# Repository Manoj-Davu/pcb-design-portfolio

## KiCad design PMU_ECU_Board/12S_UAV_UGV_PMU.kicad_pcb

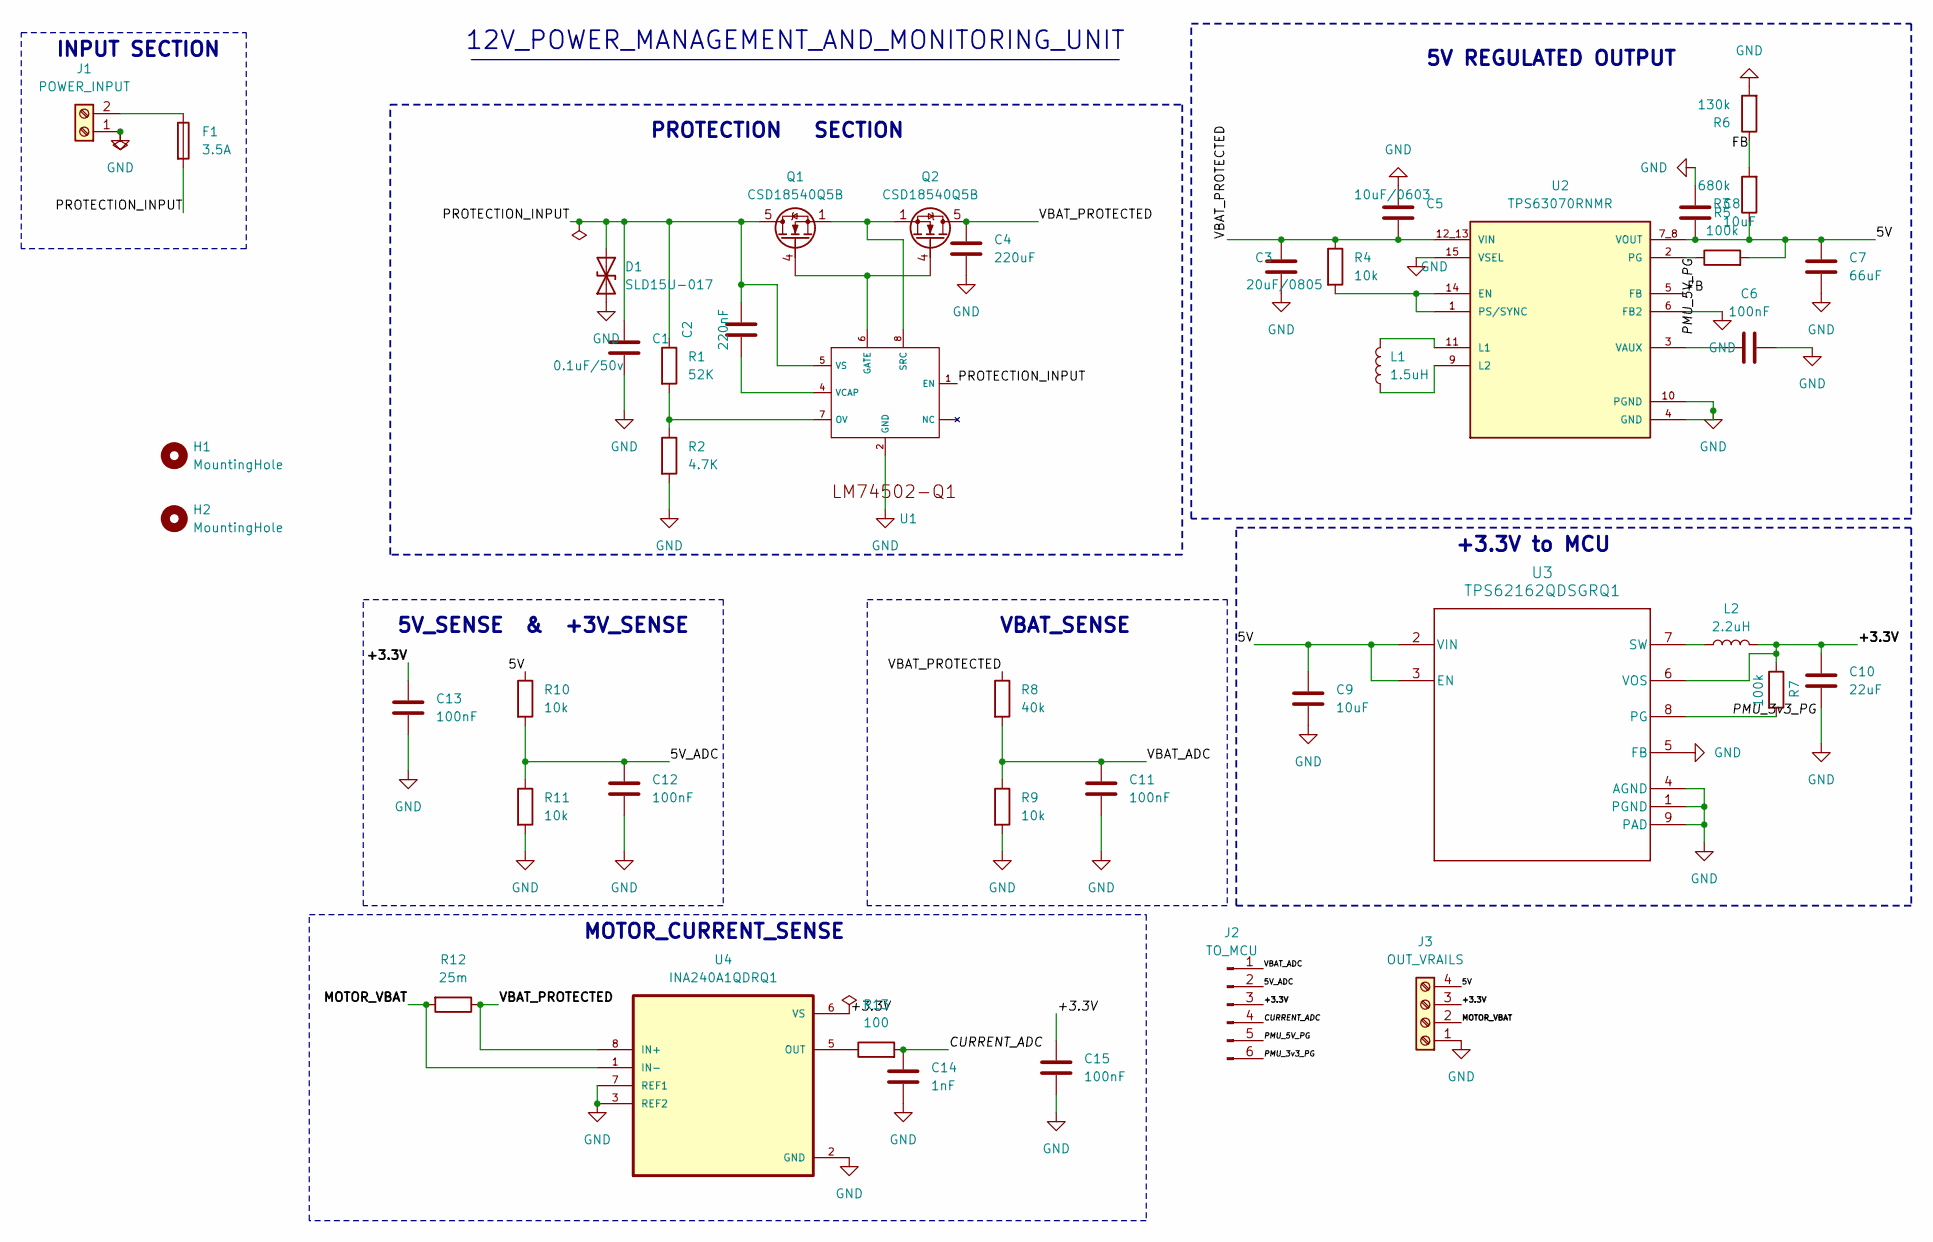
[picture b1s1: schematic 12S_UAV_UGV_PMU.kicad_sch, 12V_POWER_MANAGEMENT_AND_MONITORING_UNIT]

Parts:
C1: 0.1uF/50v; C_0603_1608Metric
C2: 220nF; C_0603_1608Metric
C3: 20uF/0805; C_0805_2012Metric
C4: 220uF; C_0603_1608Metric
C5: 10uF/0603; C_0603_1608Metric
C6, C11, C12, C13, C15: 100nF; C_0603_1608Metric
C7: 66uF; C_0805_2012Metric
C8, C9: 10uF; C_0805_2012Metric
C10: 22uF; C_0805_2012Metric
C14: 1nF; C_0603_1608Metric
D1: SLD15U-017; D_P600_R-6_P12.70mm_Horizontal
F1: 3.5A; Fuseholder_Clip-5x20mm_Littelfuse_100_Inline_P20.50x4.60mm_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
H1, H2: MountingHole; MountingHole_2.2mm_M2
J1: POWER_INPUT; TerminalBlock_Phoenix_MKDS-1,5-2-5.08_1x02_P5.08mm_Horizont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
J2: TO_MCU; PinHeader_1x06_P2.54mm_Vertical
J3: OUT_VRAILS; TerminalBlock_Phoenix_MKDS-1,5-4-5.08_1x04_P5.08mm_Horizont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
L1: 1.5uH; L_0603_1608Metric
L2: 2.2uH; L_0603_1608Metric
Q1, Q2: CSD18540Q5B; TDSON-8-1
R1: 52K; R_0603_1608Metric
R2: 4.7K; R_0603_1608Metric
R3: 680k; R_0603_1608Metric
R4, R9, R10, R11: 10k; R_0603_1608Metric
R5, R7: 100k; R_0603_1608Metric
R6: 130k; R_0603_1608Metric
R8: 40k; R_0603_1608Metric
R12: 25m; R_2512_6332Metric
R13: 100; R_0603_1608Metric
U1: SOT65P280X110-8N
U2: TPS63070RNMR; VREG_TPS63070RNMR; PARTREV B
U3: TPS62162QDSGRQ1
U4: INA240A1QDRQ1; SOIC127P599X175-8N

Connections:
/5V: C7.1, C8.2, C9.1, J3.4, R3.1, R5.2, R10.1, U2.7_8 (VOUT), U3.2 (VIN), U3.3 (EN)
/5V_ADC: C12.1, J2.2, R10.2, R11.1
/+3.3V: C10.1, C13.1, C15.1, J2.3, J3.3, L2.2, R7.1, U3.6 (VOS), U4.6 (VS)
/CURRENT_ADC: C14.1, J2.4, R13.2
/FB: R3.2, R6.1, U2.5 (FB)
/MOTOR_VBAT: J3.2, R12.2, U4.1 (IN-)
/PMU_3v3_PG: J2.6, R7.2, U3.8 (PG)
/PMU_5V_PG: J2.5, R5.1, U2.2 (PG)
/PROTECTION_INPUT: C1.1, C2.2, D1.2 (A2), F1.2, Q1.5 (D), R1.1, U1.1 (EN), U1.5 (VS)
/VBAT_ADC: C11.1, J2.1, R8.2, R9.1
/VBAT_PROTECTED: C3.1, C4.2, C5.1, Q2.5 (D), R4.1, R8.1, R12.1, U2.12_13 (VIN), U4.8 (IN+)
GND: C1.2, C3.2, C4.1, C5.2, C6.2, C7.2, C8.1, C9.2, C10.2, C11.2, C12.2, C13.2, C14.2, C15.2, D1.1 (A1), J1.1, J3.1, R2.2, R6.2, R9.2, R11.2, U1.2 (GND), U2.4 (GND), U2.6 (FB2), U2.10 (PGND), U2.15 (VSEL), U3.1 (PGND), U3.4 (AGND), U3.5 (FB), U3.9 (PAD), U4.2 (GND), U4.3 (REF2), U4.7 (REF1)
unnamed: F1.1, J1.2
unnamed: Q1.4 (G), Q2.4 (G), U1.6 (GATE)
unnamed: R1.2, R2.1, U1.7 (OV)
unnamed: Q1.1 (S), Q1.2 (S), Q1.3 (S), Q2.1 (S), Q2.2 (S), Q2.3 (S), U1.8 (SRC)
unnamed: C2.1, U1.4 (VCAP)
unnamed: R4.2, U2.1 (PS/SYNC), U2.14 (EN)
unnamed: L1.2, U2.11 (L1)
unnamed: L1.1, U2.9 (L2)
unnamed: C6.1, U2.3 (VAUX)
unnamed: L2.1, U3.7 (SW)
unnamed: R13.1, U4.5 (OUT)

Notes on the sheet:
VBAT_SENSE
INPUT SECTION
PROTECTION SECTION
5V_SENSE & +3V_SENSE
5V REGULATED OUTPUT
12V_POWER_MANAGEMENT_AND_MONITORING_UNIT
+3.3V to MCU
MOTOR_CURRENT_SENSE

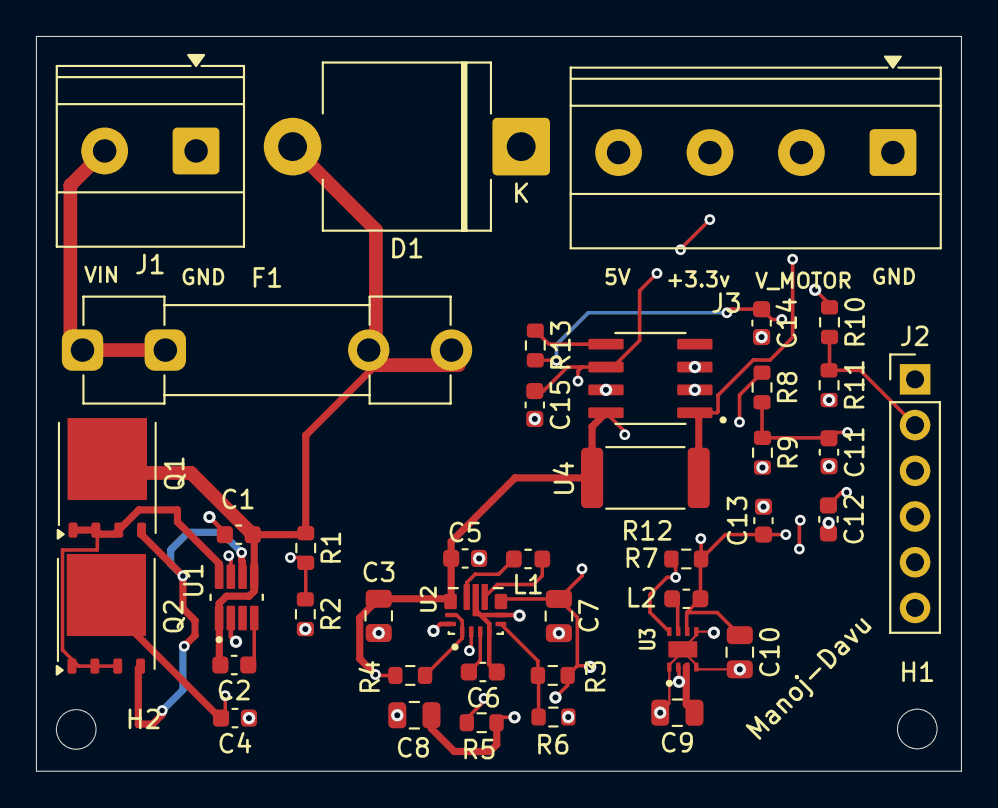
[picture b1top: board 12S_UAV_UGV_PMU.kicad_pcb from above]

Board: 4 copper layers, 51.4 x 40.8 mm, 43 parts (0 on the bottom side), 23 nets.

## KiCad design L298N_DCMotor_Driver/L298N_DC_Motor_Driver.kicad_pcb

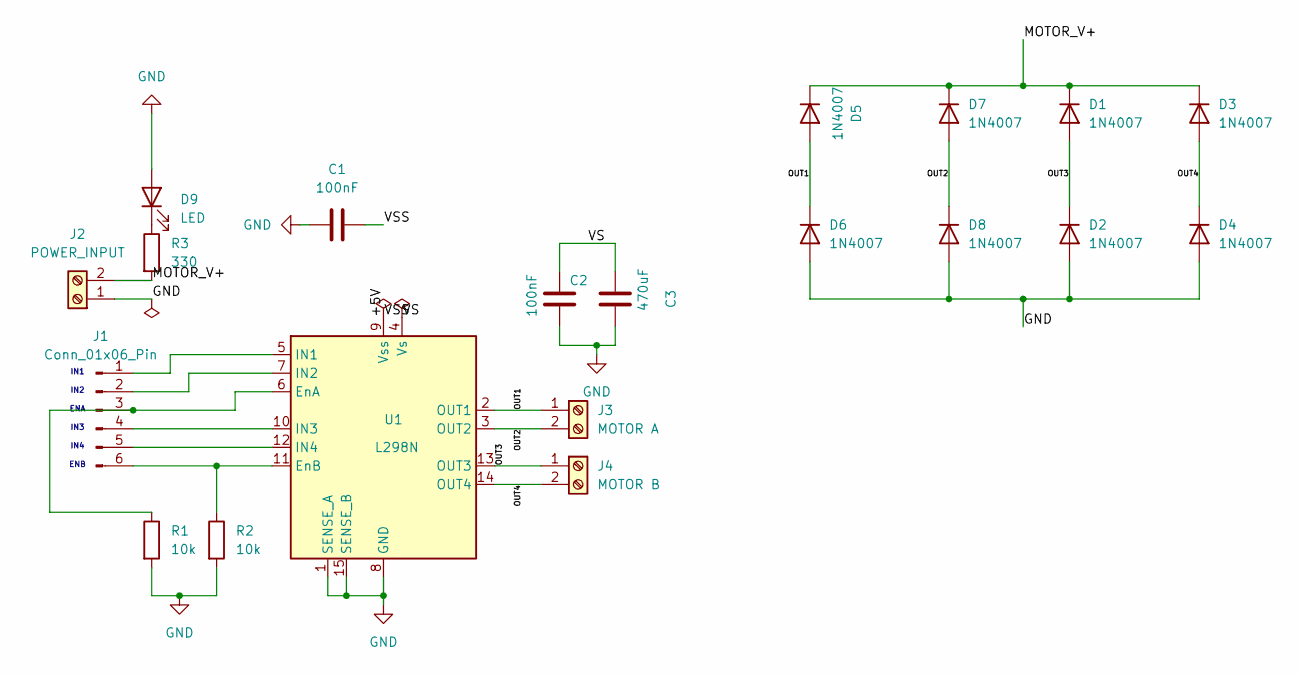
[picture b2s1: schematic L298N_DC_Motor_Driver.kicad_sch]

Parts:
C1, C2: 100nF; C_0805_2012Metric
C3: 470uF; C_0805_2012Metric
D1, D2, D3, D4, D5, D6, D7, D8: 1N4007; D_DO-41_SOD81_P10.16mm_Horizontal
D9: LED; LED_0805_2012Metric
J1: Conn_01x06_Pin; PinHeader_1x06_P2.54mm_Vertical
J2: POWER_INPUT; TerminalBlock_Phoenix_MKDS-1,5-2-5.08_1x02_P5.08mm_Horizont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
J3: MOTOR A; TerminalBlock_Phoenix_MKDS-1,5-2-5.08_1x02_P5.08mm_Horizont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
J4: MOTOR B; TerminalBlock_Phoenix_MKDS-1,5-2-5.08_1x02_P5.08mm_Horizont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
R1, R2: 10k; R_0805_2012Metric
R3: 330; R_0805_2012Metric
U1: L298N; TO-220-15_P2.54x5.08mm_StaggerOdd_Lead4.58mm_Vertical

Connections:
/+5V: C1.2, U1.9 (Vss)
/MOTOR_V+: D1.1 (K), D3.1 (K), D5.1 (K), D7.1 (K), J2.2, R3.2
/OUT1: D5.2 (A), D6.1 (K), J3.1, U1.2 (OUT1)
/OUT2: D7.2 (A), D8.1 (K), J3.2, U1.3 (OUT2)
/OUT3: D1.2 (A), D2.1 (K), J4.1, U1.13 (OUT3)
/OUT4: D3.2 (A), D4.1 (K), J4.2, U1.14 (OUT4)
/VS: C2.1, C3.1, U1.4 (Vs)
GND: C1.1, C2.2, C3.2, D2.2 (A), D4.2 (A), D6.2 (A), D8.2 (A), D9.2 (A), J2.1, R1.2, R2.2, U1.1 (SENSE_A), U1.8 (GND), U1.15 (SENSE_B)
unnamed: D9.1 (K), R3.1
unnamed: J1.1, U1.5 (IN1)
unnamed: J1.2, U1.7 (IN2)
unnamed: J1.3, R1.1, U1.6 (EnA)
unnamed: J1.4, U1.10 (IN3)
unnamed: J1.5, U1.12 (IN4)
unnamed: J1.6, R2.1, U1.11 (EnB)

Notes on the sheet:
ENA
IN2
IN3
IN4
ENB
IN1

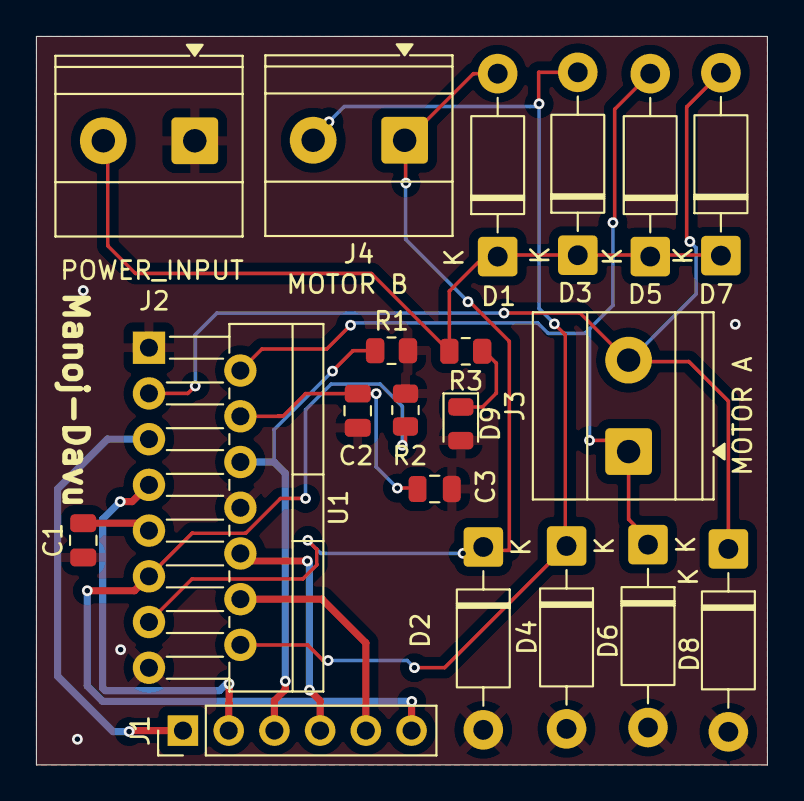
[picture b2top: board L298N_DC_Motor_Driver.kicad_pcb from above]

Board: 4 copper layers, 40.6 x 40.5 mm, 20 parts (0 on the bottom side), 15 nets.

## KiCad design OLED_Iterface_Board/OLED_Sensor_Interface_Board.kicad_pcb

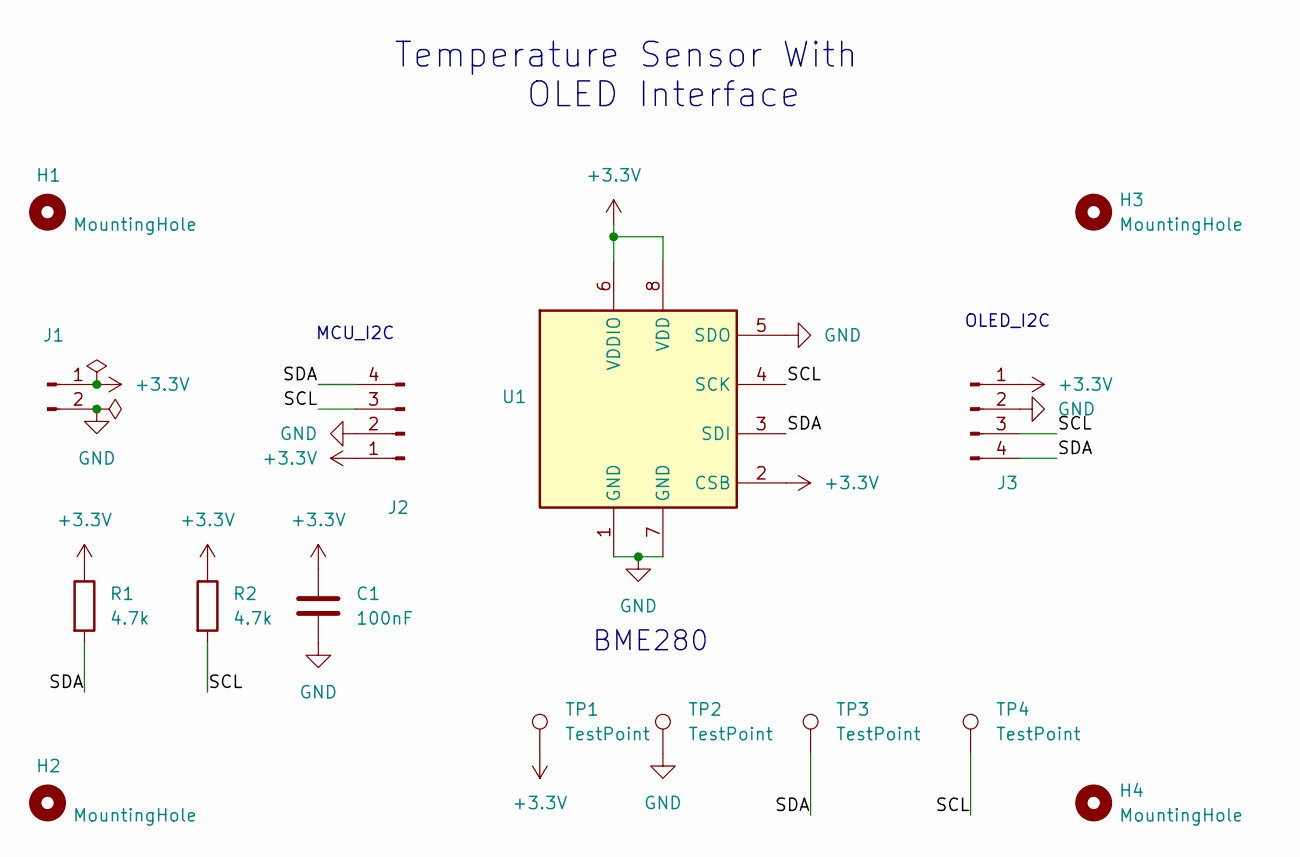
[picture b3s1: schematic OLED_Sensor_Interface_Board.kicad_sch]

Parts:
C1: 100nF; C_0603_1608Metric
H1, H2, H3, H4: MountingHole; MountingHole_3.2mm_M3
J1: POWER_IN; PinHeader_1x02_P2.54mm_Vertical
J2: MCU_I2C; PinHeader_1x04_P2.54mm_Vertical
J3: OLED_I2C; PinHeader_1x04_P2.54mm_Vertical
R1, R2: 4.7k; R_0603_1608Metric
TP1, TP2, TP3, TP4: TestPoint; TestPoint_Pad_D1.5mm
U1: BME280; Bosch_LGA-8_2.5x2.5mm_P0.65mm_ClockwisePinNumbering

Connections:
+3.3V: C1.1, J1.1, J2.1, J3.1, R1.1, R2.1, TP1.1, U1.2 (CSB), U1.6 (VDDIO), U1.8 (VDD)
/SCL: J2.3, J3.3, R2.2, TP4.1, U1.4 (SCK)
/SDA: J2.4, J3.4, R1.2, TP3.1, U1.3 (SDI)
GND: C1.2, J1.2, J2.2, J3.2, TP2.1, U1.1 (GND), U1.5 (SDO), U1.7 (GND)

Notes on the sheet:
OLED_I2C
MCU_I2C
Temperature Sensor With OLED Interface
BME280

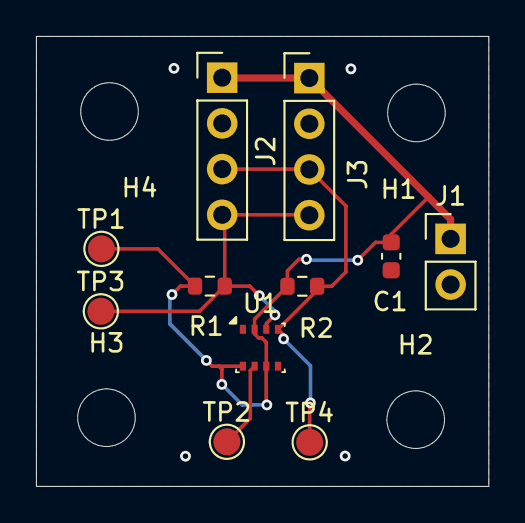
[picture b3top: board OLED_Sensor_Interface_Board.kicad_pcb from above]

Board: 4 copper layers, 25.1 x 25.0 mm, 15 parts (0 on the bottom side), 4 nets.

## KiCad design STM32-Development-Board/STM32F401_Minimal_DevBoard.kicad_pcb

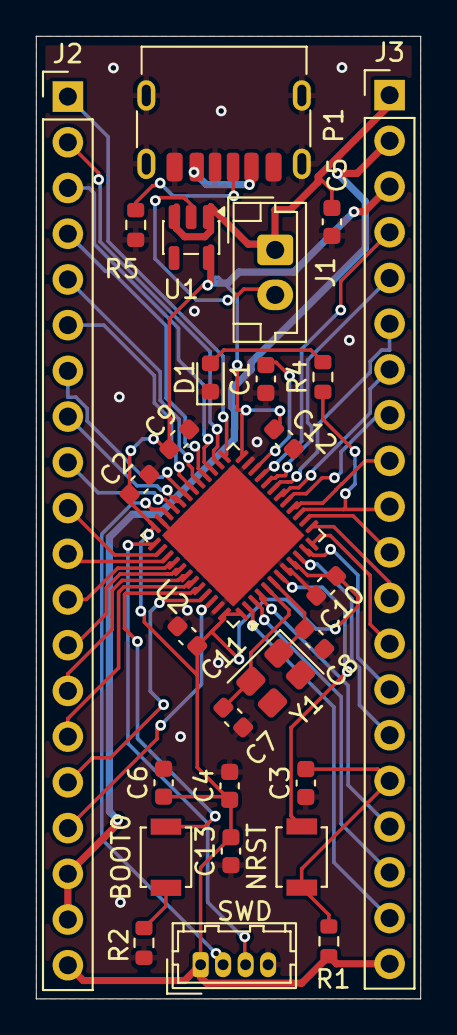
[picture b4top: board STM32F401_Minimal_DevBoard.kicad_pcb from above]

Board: 4 copper layers, 21.3 x 53.5 mm, 28 parts (0 on the bottom side), 49 nets.

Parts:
BOOT0: SW_Push; SW_SPST_B3U-1000P
C1: 2.2uF; C_0603_1608Metric
C2, C3, C10, C11, C12, C13: 100nF; C_0603_1608Metric
C4, C5, C6: 1uF; C_0603_1608Metric
C7, C8: 18pF; C_0603_1608Metric
C9: 4.7uF; C_0603_1608Metric
D1: LED; LED_0603_1608Metric
J1: POWER_IN; JST_EH_B2B-EH-A_1x02_P2.50mm_Vertical
J2, J3: Conn_01x20_Pin; PinHeader_1x20_P2.54mm_Vertical
NRST: SW_Push; SW_SPST_B3U-1000P
P1: USB_C_Plug_USB2.0; USB_C_Receptacle_HRO_TYPE-C-31-M-17
R1, R2: 10K; R_0603_1608Metric
R4: 330; R_0603_1608Metric
R5: 5.1k; R_0603_1608Metric
SWD: Conn_01x04_Pin; Hirose_DF13-04P-1.25DSA_1x04_P1.25mm_Vertical
U1: AP2112K-3.3; SOT-23-5
U2: STM32F401CCUx; QFN-48-1EP_7x7mm_P0.5mm_EP5.6x5.6mm
Y1: Crystal; Crystal_SMD_3225-4Pin_3.2x2.5mm

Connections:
+3.3V: C2.2, C4.1, C6.1, C9.1, C10.2, C11.2, C12.2, C13.2, J2.20, J3.3, J3.20, R1.1, SWD.1, U1.5 (VOUT), U2.1 (VBAT), U2.9 (VREF+), U2.24 (VDD), U2.36 (VDD), U2.48 (VDD)
+5V: P1.A9 (VBUS), P1.B9 (VBUS)
/5V: C5.2, J1.1 (5V), J3.1, U1.1 (VIN), U1.3 (EN)
/G: J2.18, J2.19, J3.2
/PA0: J3.15, U2.10 (PA0)
/PA1: J3.14, U2.11 (PA1)
/PA2: J3.13, U2.12 (PA2)
/PA3: J3.12, U2.13 (PA3)
/PA4: J3.11, U2.14 (PA4)
/PA5: J3.10, R4.1, U2.15 (PA5)
/PA6: J3.9, U2.16 (PA6)
/PA7: J3.8, U2.17 (PA7)
/PA8: J2.5, U2.29 (PA8)
/PA9: J2.6, U2.30 (PA9)
/PA10: J2.7, U2.31 (PA10)
/PA11: J2.8, U2.32 (PA11)
/PA12: J2.9, U2.33 (PA12)
/PA13: SWD.2, U2.34 (PA13)
/PA14: SWD.3, U2.37 (PA14)
/PA15: J2.10, U2.38 (PA15)
/PB0: J3.7, U2.18 (PB0)
/PB1: J3.6, U2.19 (PB1)
/PB2: J3.5, U2.20 (PB2)
/PB3: J2.11, U2.39 (PB3)
/PB4: J2.12, U2.40 (PB4)
/PB5: J2.13, U2.41 (PB5)
/PB6: J2.14, U2.42 (PB6)
/PB7: J2.15, U2.43 (PB7)
/PB8: J2.16, U2.45 (PB8)
/PB9: J2.17, U2.46 (PB9)
/PB10: J3.4, U2.21 (PB10)
/PB12: J2.1, U2.25 (PB12)
/PB13: J2.2, U2.26 (PB13)
/PB14: J2.3, U2.27 (PB14)
/PB15: J2.4, U2.28 (PB15)
/PC13: J3.19, U2.2 (PC13)
/PC14: J3.18, U2.3 (PC14)
/PC15: J3.17, U2.4 (PC15)
BOOT0: BOOT0.1, R2.1
GND: C1.1, C2.1, C3.1, C4.2, C5.1, C6.2, C7.2, C8.2, C9.2, C10.1, C11.1, C12.1, C13.1, D1.1 (K), P1.A12 (GND), P1.B5 (VCONN), P1.B12 (GND), P1.S1 (SHIELD), R2.2, R5.2, SWD.4, U2.8 (VSSA), U2.23 (VSS), U2.35 (VSS), U2.47 (VSS), U2.49 (VSS)
unnamed: D1.2 (A), R4.2
unnamed: J1.2 (GND), U1.2 (GND)
unnamed: P1.A5 (CC), R5.1
unnamed: BOOT0.2, U2.44 (BOOT0)
unnamed: NRST.2, U2.7 (NRST)
unnamed: C7.1, U2.5 (PH0), Y1.2
unnamed: C8.1, U2.6 (PH1), Y1.1
unnamed: C1.2, U2.22 (VCAP1)
RESET: C3.2, J3.16, NRST.1, R1.2
